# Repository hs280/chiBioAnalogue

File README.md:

# Chi.Bio Analogue

A variant of the [Chi.Bio](https://github.com/HarrisonSteel/ChiBio) bioreactor whose LEDs are driven by analogue constant-current regulators (CCR) with a DAC set-point, instead of digital PWM.

- `docs/ANALOGUE_LED_DESIGN.md`: the redesign, I2C map, trade-offs and bring-up steps. Start here.
- `software/`: Chi.Bio control software with an analogue LED driver (`LED_DRIVE_MODE`). `analogue-led.patch` is the diff from upstream.
- `hardware/baseline-digital/`: the original digital-LED PCB package, unchanged, as supplied.
- `hardware/source-altium/`: Side board Altium project (schematic, PCB, project) from the Chi.Bio authors, plus a KiCad import of the PCB.
- `hardware/analogue-changes/`: BOM changes for the Side board.
- `tools/`: scripts that extract the netlist from the Altium schematic and convert the PCB to KiCad.
- `tests/test_led_dac.py`: checks the DAC bytes the firmware sends, using stubbed I2C.

**Status:** the real Side board schematic is in the repo and the design is matched to it. Firmware is tested only against stubs. The modified Side board has not been laid out or fabricated. See the design document for the open items marked VERIFY.

Software is derived from Chi.Bio by Harrison Steel's group. Check the upstream repository for its licence before redistributing.

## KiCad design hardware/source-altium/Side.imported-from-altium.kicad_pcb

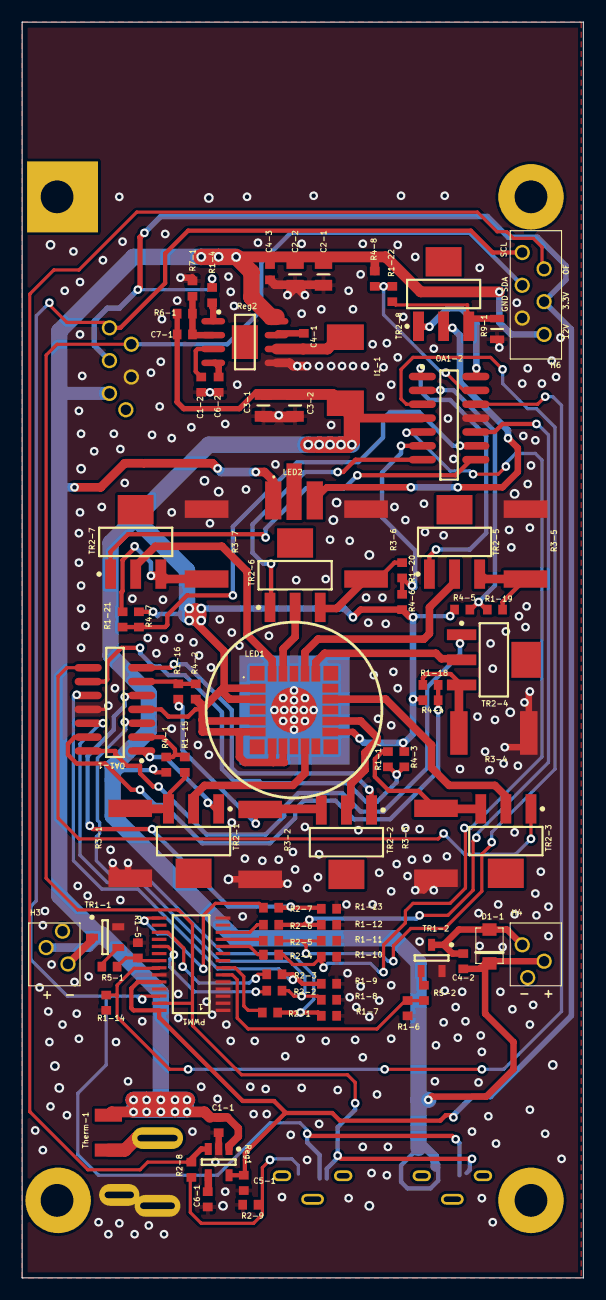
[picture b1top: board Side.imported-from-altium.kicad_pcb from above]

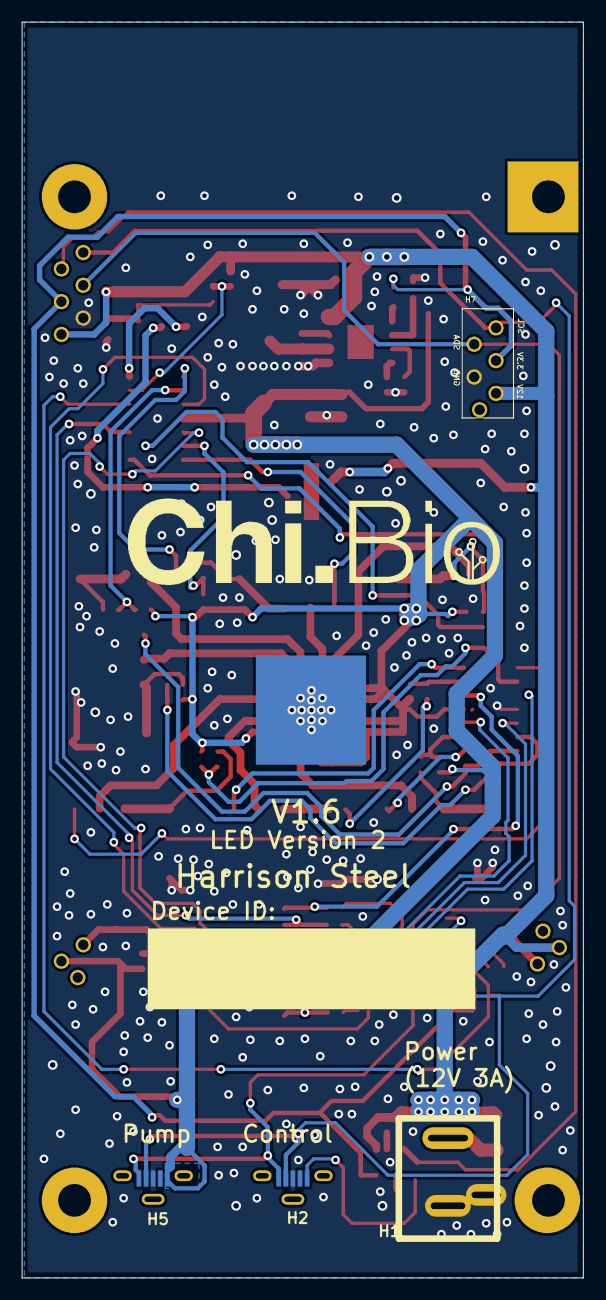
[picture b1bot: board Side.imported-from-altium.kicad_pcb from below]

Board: 2 copper layers, 51.4 x 115.0 mm, 88 parts (4 on the bottom side), 69 nets.

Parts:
C1-1, C1-2: 1 uF; 1608[0603]
C2-1, C2-2: 10 uF; 0805Large
C3-1, C3-2: 22 uF; 0805Large
C4-1, C4-2, C4-3: 0.1 uF; 1608[0603]
C5-1: 4.7uF; 1608[0603]
C6-1, C6-2: 0.01uF; 1608[0603]
C7-1: 22pF; 1608[0603]
D1-1: D1; SOD 123
H1: Power (12V 3A); PowerJack1
H2: Control; Micro USB
H3: Heat; InterCon2
H4: Stir; InterCon2
H5: Pump; Micro USB
H6: Measurement; Inter Connect 6 - reduced
H7: Expansion; Inter Connect 5
I1-1: 3.3uH; INDUCTOR2
LED1: LEDEngin_V2; LEDENGIN
LED2: LED UV; UV LED
OA1-1, OA1-2: OpAmp 4Way; SOIC14_M
PWM1: PWM28; TSSOP-28
R1-4, R1-5, R1-6, R1-7, R1-8, R1-9, R1-10, R1-11, R1-12, R1-13, R1-14, R1-15, R1-16, R1-17, R1-18, R1-19, R1-20, R1-21, R1-22: 10k; 1608[0603]
R2-1, R2-2, R2-3, R2-4, R2-5, R2-6, R2-7, R2-8, R2-9: 38.3k; 1608[0603]
R3-1, R3-2, R3-3, R3-4, R3-5, R3-6, R3-7: 1; 2512
R4-1, R4-2, R4-3, R4-4, R4-5, R4-6, R4-7, R4-8: 1M; 1608[0603]
R5-1, R5-2: 4.99; 1608[0603]
R6-1: 152k; 1608[0603]
R7-1: 22.1k; 1608[0603]
R9-1: 40.2; 0805
Reg1: 3.3V Regulator; SOT23-5
Reg2: 6V Regulator; 8-SOIC V3
TR1-1, TR1-2: MOSFET; SOT23-3
TR2-1, TR2-2, TR2-3, TR2-4, TR2-5, TR2-6, TR2-7, TR2-8: TransistorPower2; SOT223_M
Therm-1: 10; 1206

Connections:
3.3V: C5-1.1, H6.3, H7.3, PWM1.24, PWM1.28, R1-4.1, Reg1.5
6V: C3-1.2, C3-2.2, C4-2.1, C7-1.2, D1-1.1, H4.1, H5.5, I1-1.2, LED1.2, LED1.3, LED1.5, LED1.6, LED1.8, LED1.9, LED1.14, OA1-1.4, OA1-2.4, R4-1.1, R4-2.1, R4-3.1, R4-4.1, R4-5.1, R4-6.1, R4-7.1, R6-1.1
12VRaw: C1-1.1, C2-1.2, C2-2.2, C4-3.1, H3.1, H6.1, H7.1, LED2.2, R4-8.1, Reg1.1, Reg2.8, Therm-1.2
Blue: LED1.23, TR2-6.2
Blue0: PWM1.10, R2-4.2
Blue1: OA1-2.5, R1-10.2, R2-4.1
Cyan: LED1.11, TR2-1.2
Cyan0: PWM1.7, R2-1.2
Cyan1: OA1-1.3, R1-7.2, R2-1.1
Enable: H2.5, R2-8.1, R2-9.2
GND: C1-1.2, C1-2.2, C2-1.1, C2-2.1, C3-1.1, C3-2.1, C4-3.2, C5-1.2, C6-1.1, C6-2.2, H1.2, H1.3, H2.3, H5.3, H6.2, H7.2, OA1-1.11, OA1-2.11, PWM1.1, PWM1.2, PWM1.3, PWM1.4, PWM1.5, PWM1.14, PWM1.23, PWM1.25, R1-5.1, R1-6.1, R1-7.1, R1-8.1, R1-9.1, R1-10.1, R1-11.1, R1-12.1, R1-13.1, R1-14.1, R2-9.1, R3-1.1, R3-2.1, R3-3.1, R3-4.1, R3-5.1, R3-6.1, R3-7.1, R7-1.1, R9-1.1, Reg1.2, Reg2.5, TR1-1.2, TR1-2.2
Green: LED1.21, TR2-5.2
Green0: PWM1.11, R2-5.2
Green1: OA1-2.3, R1-11.2, R2-5.1
Lime1: LED1.20, TR2-4.2
Lime2: LED1.17, TR2-3.2
Lime10: PWM1.19, R2-2.2
Lime11: OA1-1.12, R1-8.2, R2-2.1
Lime20: PWM1.17, R2-3.2
Lime22: OA1-1.10, R1-9.2, R2-3.1
NetC1-2_1: C1-2.1, Reg2.3
NetC4-1_1: C4-1.1, I1-1.1, Reg2.6
NetC4-1_2: C4-1.2, Reg2.7
NetC4-2_2: C4-2.2, D1-1.2, H4.2, TR1-2.3
NetC6-1_2: C6-1.2, Reg1.4
NetC6-2_1: C6-2.1, Reg2.4
NetC7-1_1: C7-1.1, R6-1.2, R7-1.2, Reg2.2
NetH1_1: H1.1, Therm-1.1
NetH3_2: H3.2, TR1-1.3
NetLED2_1: LED2.1, TR2-8.2
NetOA1-1_1: OA1-1.1, TR2-1.1
NetOA1-1_2: OA1-1.2, R1-15.1, R4-1.2
NetOA1-1_6: OA1-1.6, R1-16.1, R4-2.2
NetOA1-1_7: OA1-1.7, TR2-2.1
NetOA1-1_8: OA1-1.8, TR2-3.1
NetOA1-1_9: OA1-1.9, R1-17.1, R4-3.2
NetOA1-1_13: OA1-1.13, R1-18.1, R4-4.2
NetOA1-1_14: OA1-1.14, TR2-4.1
NetOA1-2_1: OA1-2.1, TR2-5.1
NetOA1-2_2: OA1-2.2, R1-19.1, R4-5.2
NetOA1-2_6: OA1-2.6, R1-20.1, R4-6.2
NetOA1-2_7: OA1-2.7, TR2-6.1
NetOA1-2_8: OA1-2.8, TR2-7.1
NetOA1-2_9: OA1-2.9, R1-21.1, R4-7.2
NetOA1-2_12: OA1-2.12, PWM1.22, R1-14.2
NetOA1-2_13: OA1-2.13, R1-22.2, R4-8.2
NetOA1-2_14: OA1-2.14, TR2-8.1
NetPWM1_6: PWM1.6, R1-6.2, R5-2.1
NetPWM1_21: PWM1.21, R1-5.2, R5-1.1
NetR1-4_2: R1-4.2, Reg2.1
NetR1-15_2: R1-15.2, R3-1.2, TR2-1.3
NetR1-16_2: R1-16.2, R3-2.2, TR2-2.3
NetR1-17_2: R1-17.2, R3-3.2, TR2-3.3
NetR1-18_2: R1-18.2, R3-4.2, TR2-4.3
NetR1-19_2: R1-19.2, R3-5.2, TR2-5.3
NetR1-20_2: R1-20.2, R3-6.2, TR2-6.3
NetR1-21_2: R1-21.2, R3-7.2, TR2-7.3
NetR1-22_1: R1-22.1, R9-1.2, TR2-8.3
NetR5-1_2: R5-1.2, TR1-1.1
NetR5-2_2: R5-2.2, TR1-2.1
Overflow: H6.5, R2-8.2, Reg1.3
Red: LED1.24, TR2-7.2
Red0: PWM1.12, R2-6.2
Red1: OA1-2.10, R1-12.2, R2-6.1
SCL: H2.2, H5.2, H6.6, H7.5, PWM1.26
SDA: H2.1, H5.1, H6.4, H7.4, PWM1.27
Yellow: LED1.15, TR2-2.2
Yellow0: PWM1.15, R2-7.2
Yellow1: OA1-1.5, R1-13.2, R2-7.1
